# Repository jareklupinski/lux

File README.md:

# lux
A fun gadget to light the way

A neat design for an idea I had to make an accelerometer-reactive flashlight.

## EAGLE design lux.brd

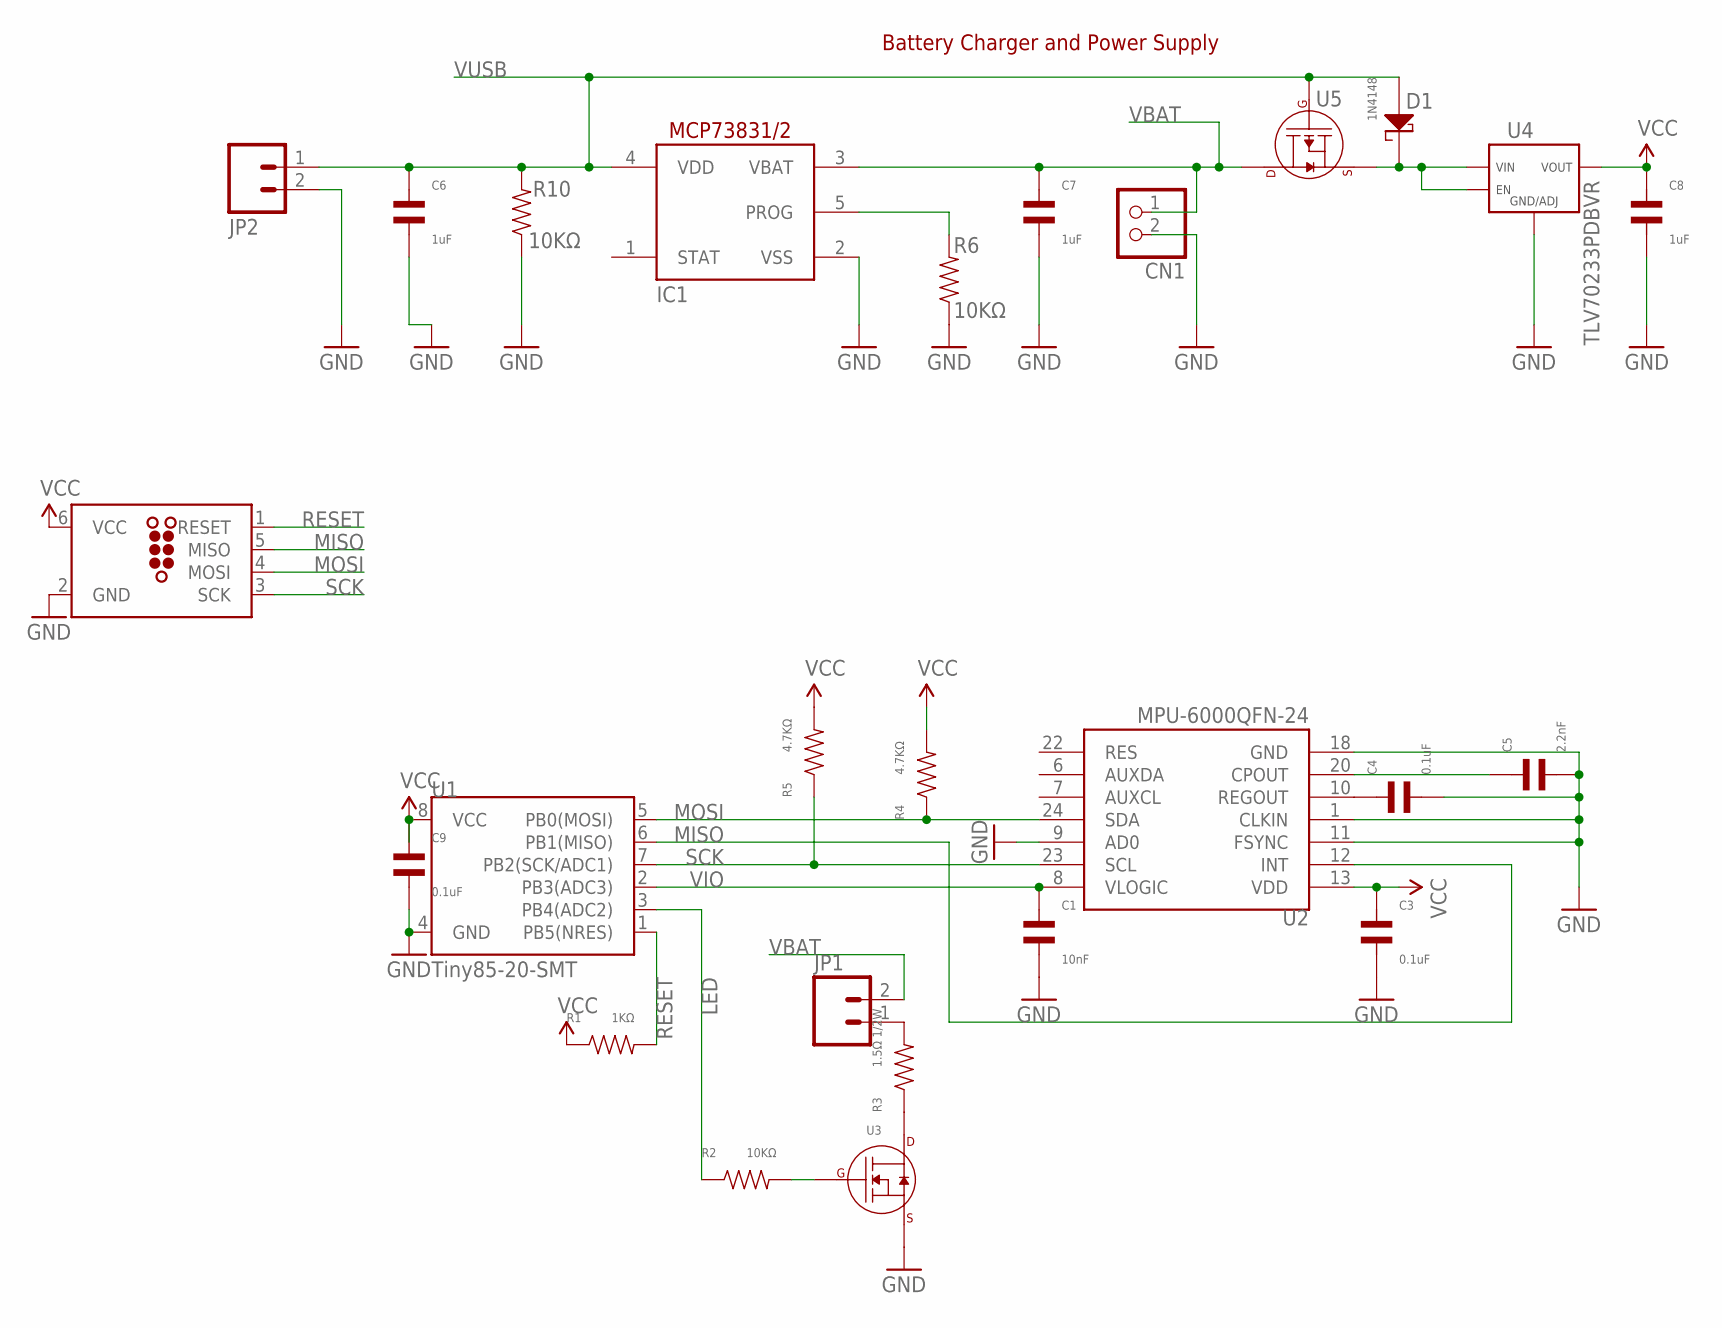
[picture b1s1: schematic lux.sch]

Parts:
C1: 10nF; C0805
C3, C4, C9: 0.1uF; C0805
C5: 2.2nF; C0805
C6, C7, C8: 1uF; C0805
CN1: JST_2PIN-SMT-RA; JST-PH-2-SMT-RA
D1: 1N4148; SOD-123
IC1: MCP73831/OT; SOT23-5L
J1: TC2030-MCP-NLFIX; TC2030-MCP-NL
JP1, JP2: M02PTH; 1X02
R1: 1KΩ; R0805
R2, R6, R10: 10KΩ; R0805
R3: 1.5Ω 1/2W; R0805
R4, R5: 4.7KΩ; R0805
U1: Tiny85-20-SMT; SO08-EIAJ
U2: MPU-6000QFN-24; QFN-24-TESTING
U3: N-CHANNEL_FET_SOT-23-3; SOT-23-3
U4: TLV70233PDBVR; SOT-23-5
U5: P-CHANNEL_FET_SOT-23-3; SOT-23-3

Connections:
GND: C1.P$2, C3.P$2, C4.P$2, C5.P$2, C6.P$2, C7.P$2, C8.P$2, C9.P$2, CN1.2 (1), IC1.2 (VSS), J1.2 (GND), JP2.2, R6.P$1, R10.P$1, U1.4 (GND), U2.1 (CLKIN), U2.9 (AD0), U2.11 (FSYNC), U2.18 (GND), U3.P$2 (SOURCE), U4.P$2 (GND/ADJ)
LED: R2.P$1, U1.3 (PB4(ADC2))
MISO: J1.5 (MISO), U1.6 (PB1(MISO)), U2.12 (INT)
MOSI: J1.4 (MOSI), R4.P$1, U1.5 (PB0(MOSI)), U2.24 (SDA)
unnamed: R3.P$1, U3.P$3 (DRAIN)
unnamed: R2.P$2, U3.P$1 (GATE)
unnamed: C4.P$1, U2.10 (REGOUT)
unnamed: JP1.1, R3.P$2
unnamed: C5.P$1, U2.20 (CPOUT)
unnamed: IC1.5 (PROG), R6.P$2
RESET: J1.1 (RESET), R1.P$2, U1.1 (PB5(NRES))
SCK: J1.3 (SCK), R5.P$1, U1.7 (PB2(SCK/ADC1)), U2.23 (SCL)
UC_VCC: D1.CATHODE, U4.P$1 (VIN), U4.P$3 (EN), U5.P$2 (SOURCE)
VBAT: C7.P$1, CN1.1 (2), IC1.3 (VBAT), JP1.2, U5.P$3 (DRAIN)
VCC: C3.P$1, C8.P$1, C9.P$1, J1.6 (VCC), R1.P$1, R4.P$2, R5.P$2, U1.8 (VCC), U2.13 (VDD), U4.P$5 (VOUT)
VIO: C1.P$1, U1.2 (PB3(ADC3)), U2.8 (VLOGIC)
VUSB: C6.P$1, D1.ANODE, IC1.4 (VDD), JP2.1, R10.P$2, U5.P$1 (GATE)

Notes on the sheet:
Battery Charger and Power Supply

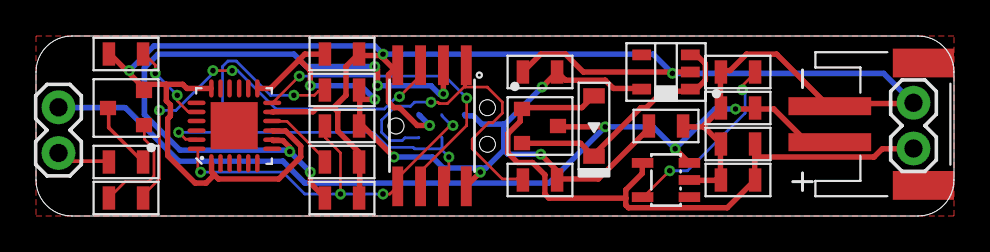
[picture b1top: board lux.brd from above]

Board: 2 copper layers, 51.0 x 10.0 mm, 26 parts (1 on the bottom side), 17 nets.

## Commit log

2018-07-06 design tested: working

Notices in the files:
parts and their libraries:
SparkFun-DigitalIC: Licensing: CC v3.0 Share-Alike You are welcome to use this library for commercial purposes.
sonik: ©2009 ROFA.cz - modified and updated by Robert Darlington ‹rdarlington@gmail.com›
